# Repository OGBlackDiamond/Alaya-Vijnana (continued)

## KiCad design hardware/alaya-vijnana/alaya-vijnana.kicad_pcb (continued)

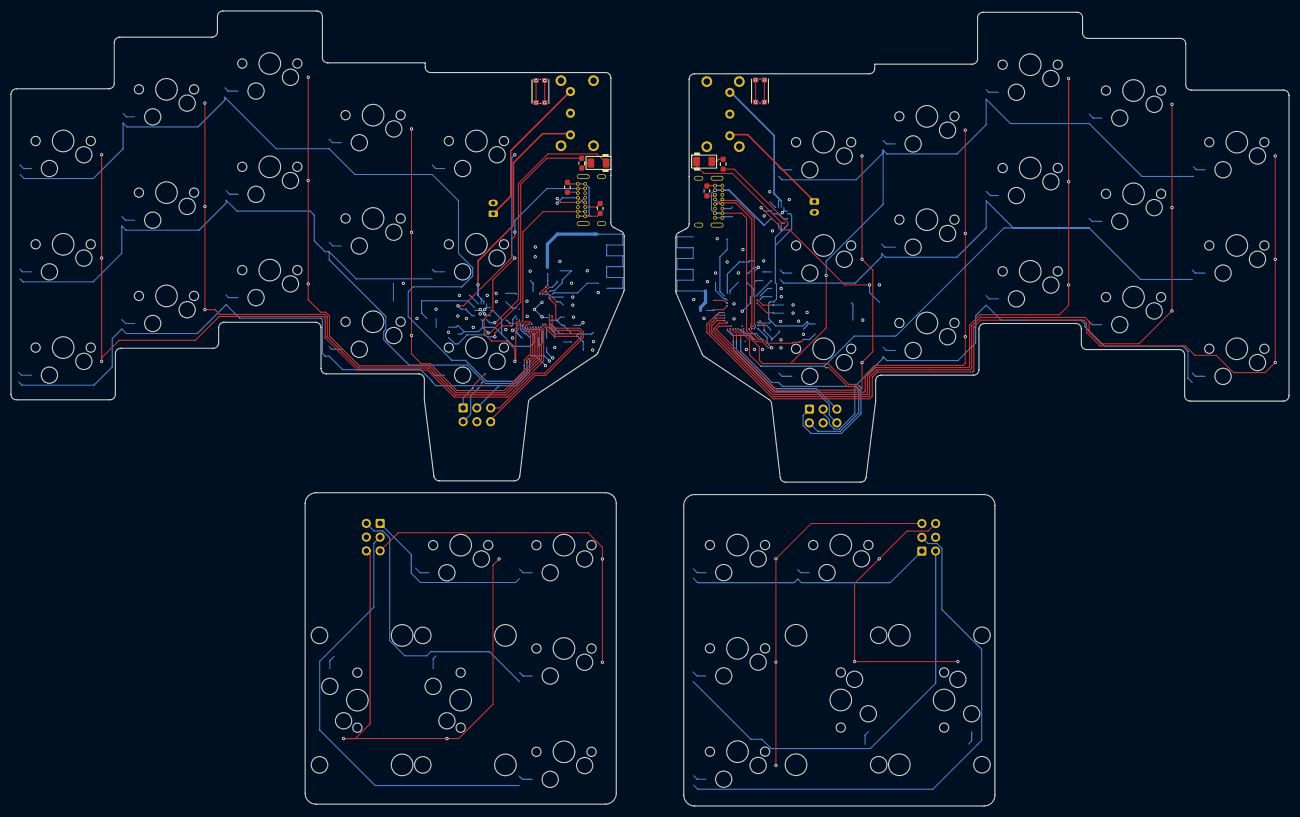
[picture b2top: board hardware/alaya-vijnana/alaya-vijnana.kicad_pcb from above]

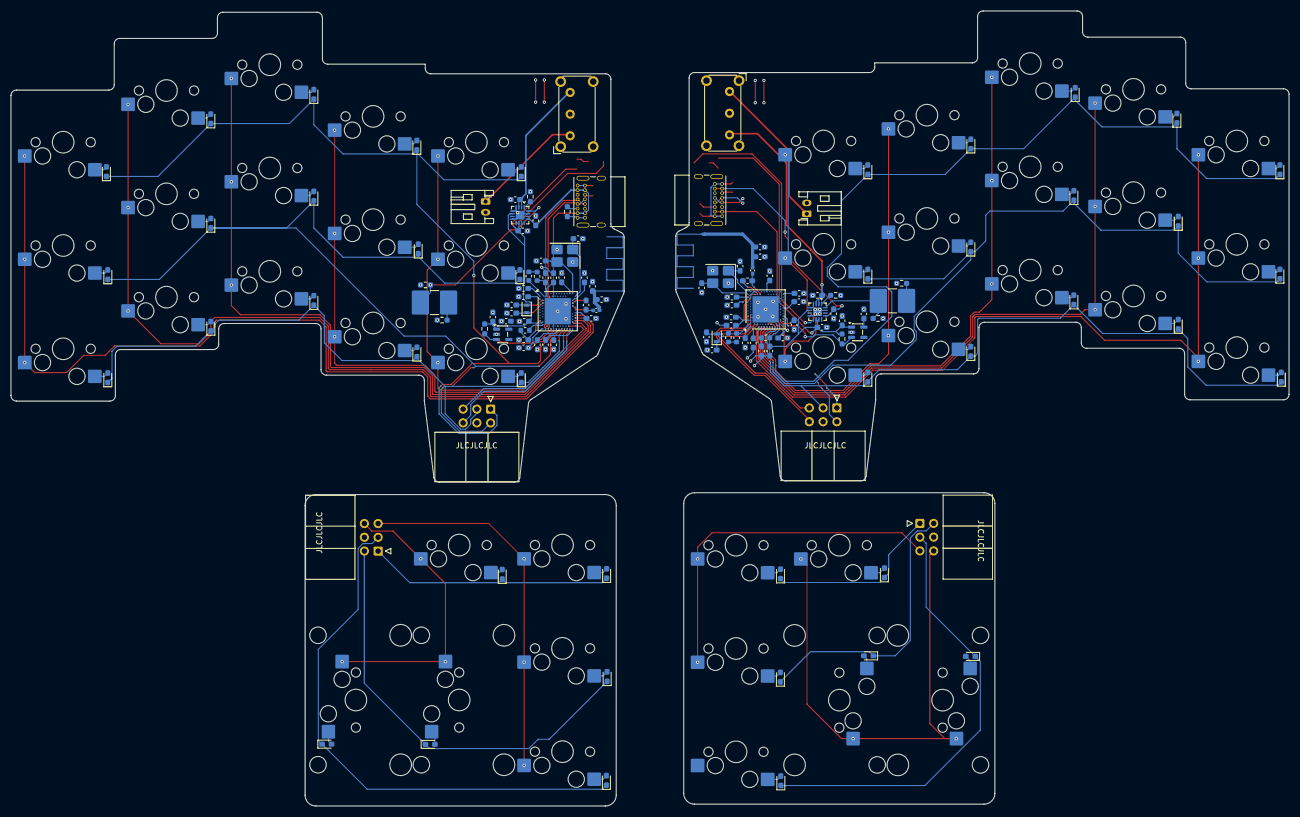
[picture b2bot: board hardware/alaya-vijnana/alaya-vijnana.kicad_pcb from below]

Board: 4 copper layers, 235.7 x 146.6 mm, 182 parts (173 on the bottom side), 135 nets.

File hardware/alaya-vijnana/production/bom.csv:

Designator,Footprint,Quantity,Value,LCSC Part #
"C1, C2, C23, C24, C31, C32, C41, C42",0603,8,12pF,
"C10, C11, C33, C34",0603,4,100pF,
"C12, C35",0603,2,820pF,
"C13, C16, C17, C22, C25, C30, C36, C37, C38, C4, C45, C46, C47, C5",0603,14,4.7uF,
"C14, C18, C26, C3, C39, C44",0603,6,1uF,
"C15, C40",0603,2,47nF,
"C19, C20, C21, C27, C28, C29",0603,6,100nF,
"C43, C9",0603,2,10uF,
"C48, C6",0603,2,0.8pF,
"C49, C7",0603,2,0.5pF,
"C50, C8",0603,2,N.C.,
"D1, D10, D11, D12, D13, D14, D15, D16, D17, D18, D19, D2, D20, D21, D22, D23, D24, D25, D26, D27, D28, D29, D3, D30, D31, D32, D33, D34, D35, D36, D37, D38, D39, D4, D40, D41, D42, D5, D6, D7, D8, D9",0603,42,D,
"J1, J3",JST_PH_S2B-PH-K_1x02_P2.00mm_Horizontal,2,Bat,
"J2, J4",USB_C_Receptacle_GCT_USB4085,2,USB_C_Receptacle_USB2.0_16P,
"J5, J6",IDC-Header_2x03_P2.54mm_Horizontal,2,MAIN_CONN,
"J7, J8",IDC-Header_2x03_P2.54mm_Horizontal,2,CLUSTER_CONN,
"L1, L8",0402,2,4.7nH,
"L2, L4, L6, L7",0603,4,10uH,
"L3, L5",0603,2,15nH,
"LED1, LED2",1206,2,Charge_LED,
"R1, R8",0603,2,2k,
"R10, R5",0603,2,10M,
"R11, R12, R2, R3, R4, R9",0603,6,10k,
"R13, R14, R6, R7",0603,4,5.1k,
"SW1, SW23",SW_E-Switch_EG1224_SPDT_Angled,2,Power_Switch,
"SW10, SW11, SW12, SW13, SW14, SW15, SW16, SW17, SW2, SW20, SW21, SW22, SW24, SW25, SW26, SW27, SW28, SW29, SW3, SW30, SW31, SW32, SW33, SW34, SW35, SW36, SW37, SW38, SW39, SW4, SW42, SW43, SW44, SW5, SW6, SW7, SW8, SW9",MX-Hotswap-1U,38,MX HotSwap,
"SW18, SW19, SW40, SW41",MX-Hotswap-2U,4,MX HotSwap,
"TP1, TP2",2816,2,Charge Boost,
"U1, U4",Nordic_AQFN-73-1EP_7x7mm_P0.5mm,2,nRF52840,
"U2, U6",VQFN-16-1EP_3x3mm_P0.5mm_EP1.6x1.6mm,2,BQ24075RGT,
"U3, U5",SOT-23-5,2,XC6220B331MR,
"X1, X2",Crystal_SMD_2012-2Pin_2.0x1.2mm,2,32.768kHz,
"Y1, Y2",Crystal_SMD_3225-4Pin_3.2x2.5mm_HandSoldering,2,32Mhz,

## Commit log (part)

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2025-12-19 made left half
2025-12-19 schematics done outside of cluster to main connectors, PCB laid out
2025-12-19 finished key wiring w/ connectors
2025-12-19 added pcb antenna
2025-12-21 left side wired up
2025-12-22 finished
2025-12-22 fixed everything
2025-12-27 split into parts
2026-01-07 added firmware
2026-01-07 removed excess
2026-01-07 removed software
2026-01-07 readded software
2026-01-24 production stuff
2026-01-26 added 3d model
2026-01-26 again
2026-01-26 correct
2026-01-26 more correct
2026-01-29 finished left main plate
2026-01-29 corrected cad
2026-05-18 lots of work for one side
2026-06-08 started routing left side
2026-06-11 lots more routing
2026-06-25 left side done
